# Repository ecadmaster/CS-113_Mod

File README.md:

# Modernización del Manipulador Robótico CS-113 / RS-2200 Pro-Arm

Este proyecto tiene como objetivo la recuperación y actualización tecnológica de los brazos robóticos CS-113 (RS-2200 Pro-Arm) pertenecientes a la [Universidad de Los Andes (ULA)](http://ula.ve/). Mediante el estudio del esquema original y la migración a herramientas modernas como [KiCad EDA](https://www.kicad.org/), se ha diseñado un método para interceptar el bus de control original y sustituir el microprocesador [Zilog Z80](https://www.zilog.com/docs/z80/um0080.pdf) por [microcontroladores](https://es.wikipedia.org/wiki/Microcontrolador)/[SoC](https://es.wikipedia.org/wiki/Sistema_en_un_chip) de nueva generación.

## Descripción del Proyecto

Los manipuladores robóticos CS-113 fueron equipos estándar en laboratorios de robótica, pero su dependencia del [puerto paralelo (LPT)](https://es.wikipedia.org/wiki/Puerto_paralelo) y del microprocesador Z80 los hace difícilmente integrables en entornos actuales.

Este desarrollo propone:

- Ingeniería Inversa: Estudio del esquema original de la placa rotulada como DT-001.
- Migración CAD: Reconstrucción del esquema en KiCad EDA para facilitar el análisis de interconexiones.
- Intercepción de Bus: Remoción de los [ICs](https://es.wikipedia.org/wiki/Circuito_integrado) [Zilog Z80](https://www.zilog.com/docs/z80/um0080.pdf) ($$C4$$ renombrado como $$uC4$$) y [74LS04](https://www.ti.com/lit/ds/symlink/sn74ls04.pdf) ($$D7$$ renombrado como $$uD7$$) para inyectar señales de control desde un controlador externo.
- Control Moderno: Uso de una tarjeta [MikroElectronika EasyPIC6](https://www.microchip.com/en-us/development-tool/tmik003) actualizada con un microcontrolador [Microchip PIC18F46K40](https://www.microchip.com/en-us/product/pic18f46k40).

## Esquemas

La [placa base](https://es.wikipedia.org/wiki/Circuito_impreso) del manipulador se encuentra ubicada por la parte inferior del mismo.

### Esquema original

El circuito disponible en la pagina #13 del documento [RS-2200_Pro-Arm_Robotics](datasheet/RS-2200_Pro-Arm_Robotics.pdf), entre otros valores interesantes que se logran conseguir allí de éste aparato.

### Esquema migrado a KiCad EDA

El esquema migrado a una herramienta de diseño es como sigue:

## Hardware y Modificaciones

### Componentes Reutilizados (Bloque de Potencia)

La placa original utiliza una arquitectura lógica robusta que se mantiene para el manejo de los motores, para ello se requiere la comprensión de los siguientes elementos:

- [74LS245](https://www.ti.com/lit/ds/symlink/sn74ls245.pdf): Transceptores de bus octales.
- [74LS138](https://www.ti.com/lit/ds/symlink/sn74ls138.pdf): Decodificador/demultiplexor de 3 a 8 líneas.
- [74LS75](https://www.ti.com/lit/ds/symlink/sn74ls75.pdf): Latches biestables de 4 bits.
- [TD62064AP](https://mm.digikey.com/Volume0/opasdata/d220001/medias/docus/932/TD62064AP%2CAF.pdf): Drivers [Darlington](https://es.wikipedia.org/wiki/Transistor_Darlington) de alta corriente para los [motores paso a paso (Stepper)](https://es.wikipedia.org/wiki/Motor_paso_a_paso) de tipo unipolar.

Una vez consolidado ese estudio y analizando la etapa de potencia, prácticamente solo se requiere el uso de lo siguiente:

Lo anterior sugiere que los IC: $$uC7$$, $$uE1$$, $$uE2$$, $$uE3$$, $$uE4$$, $$uE5$$, $$uE6$$, $$uE7$$, $$uF0$$, $$uF1$$, $$uF2$$, $$uF3$$, $$uF4$$, $$uF5$$, $$uF6$$, $$uF7$$ y $$uF8$$ deban estar debidamente colocados.

Tambien es requerido remover los ICs: $$uA6$$, $$uA8$$, $$uB8$$, $$uC4$$(Z80), $$uD1$$, $$uD3$$, $$uD4$$, $$uD6$$ y $$uD7$$ y $$uD7$$ para no interferir con las señales externas que provengan del controlador externo.

### Interfaz de Conexión (DB9 Personalizado)

Se ha implementado una conexión mediante un conector DB9 macho para el control de los 6 motores de paso y funciones adicionales:

| DB9 Macho | Etiqueta | Conexión |
| :----------- | :----------- | :----------- |
| Pin 1	| d0 | $$uC4$$ pin #14 |
| Pin 2	| d1 | $$uC4$$ pin #15 |
| Pin 3	| d2 | $$uC4$$ pin #12 |
| Pin 4	| d3 | $$uC4$$ pin #8 |
| Pin 5	| d4 | $$uC4$$ pin #7 |
| Pin 6	| d5 | $$uC4$$ pin #9 |
| Pin 7	| d6 | $$uC4$$ pin #10 |
| Pin 8	| ENdrv | $$uD7$$ pin #4 |
| Pin 9	| GND | $$uD7$$ pin #7 |

Quedando la modificación como sigue:

Una propuesta de adaptación en la parte trasera es como sigue:

El circuito que maneja el tren de potencia funciona con 5V TTL dado que todas las señales son de tipo entrada. Pueden conectarse controladores que funcionen a 3.3V directo sin necesidad de circuitos de interfaz, considere revisar los voltajes admitidos, ver [Logic Guide](https://www.ti.com/lit/sg/sdyu001ab/sdyu001ab.pdf) (de Texas Instruments) para mayor detalle y videoclase [Circuitos Interfaz](https://youtu.be/W1FWi5FtGR8).

## Desarrollo de Software

El firmware actual está siendo desarrollado para el [PIC18F46K40](https://www.microchip.com/en-us/product/pic18f46k40) utilizando:

- [MPLAB X IDE](https://www.microchip.com/en-us/tools-resources/develop/mplab-x-ide) con compilador [XC8](https://www.microchip.com/en-us/tools-resources/develop/mplab-xc-compilers/xc8).
- [MPLAB Code Configurator (MCC)](https://www.microchip.com/en-us/tools-resources/configure/mplab-code-configurator) para la configuración de periféricos.
- Capacidad de operación autónoma, asistida o vía [USB](https://es.wikipedia.org/wiki/Universal_Serial_Bus).

## Enlaces de Interés y Referencias

Proyectos y documentación relacionada que han servido de base:

- [Repositorio Digital ULA, Diseño e implementación de tarjeta de control para un brazo robotico CS-113, que se controle via USB](http://bdigital2.ula.ve:8080/xmlui/handle/654321/11944)
- [Análisis Técnico ITC](https://itc.ktu.lt/index.php/ITC/article/view/985/1054)
- [Hilo en Arduino Forum - Reconstrucción CS-113](https://forum.arduino.cc/t/reconstruccion-de-robot-cs-113/483691)
- [CS-113 Service-Arm](https://openvrg.moodlehub.com/file.php/30/cyr_0204/cyr_01/robotica/cs113.htm)
- [Hackaday.io - Robot Arm CS-113 Project](https://hackaday.io/project/168093-robot-arm-cs-113-18f4550-pic-usb-pc-controller)

Nota: Si has realizado algún intento de desarrollo con este manipulador, te invitamos a colaborar agregando tu referencia en esta sección.

## Colaboradores
- [Alberto Medrano](https://github.com/ecadmaster/)
- Francisco Viloria
- Gerardo Rueda
- Luis Araujo

## Instalación y Uso

Clona el repositorio:

```git clone https://github.com/ecadmaster/CS-113_Mod.git```

Consulta las datasheets para entender los límites operativos de los integrados.

## Contribuciones y Licencia
Este proyecto está bajo la licencia MIT. Las sugerencias de mejora para el entorno académico de la Escuela de Ingeniería Eléctrica son bienvenidas.

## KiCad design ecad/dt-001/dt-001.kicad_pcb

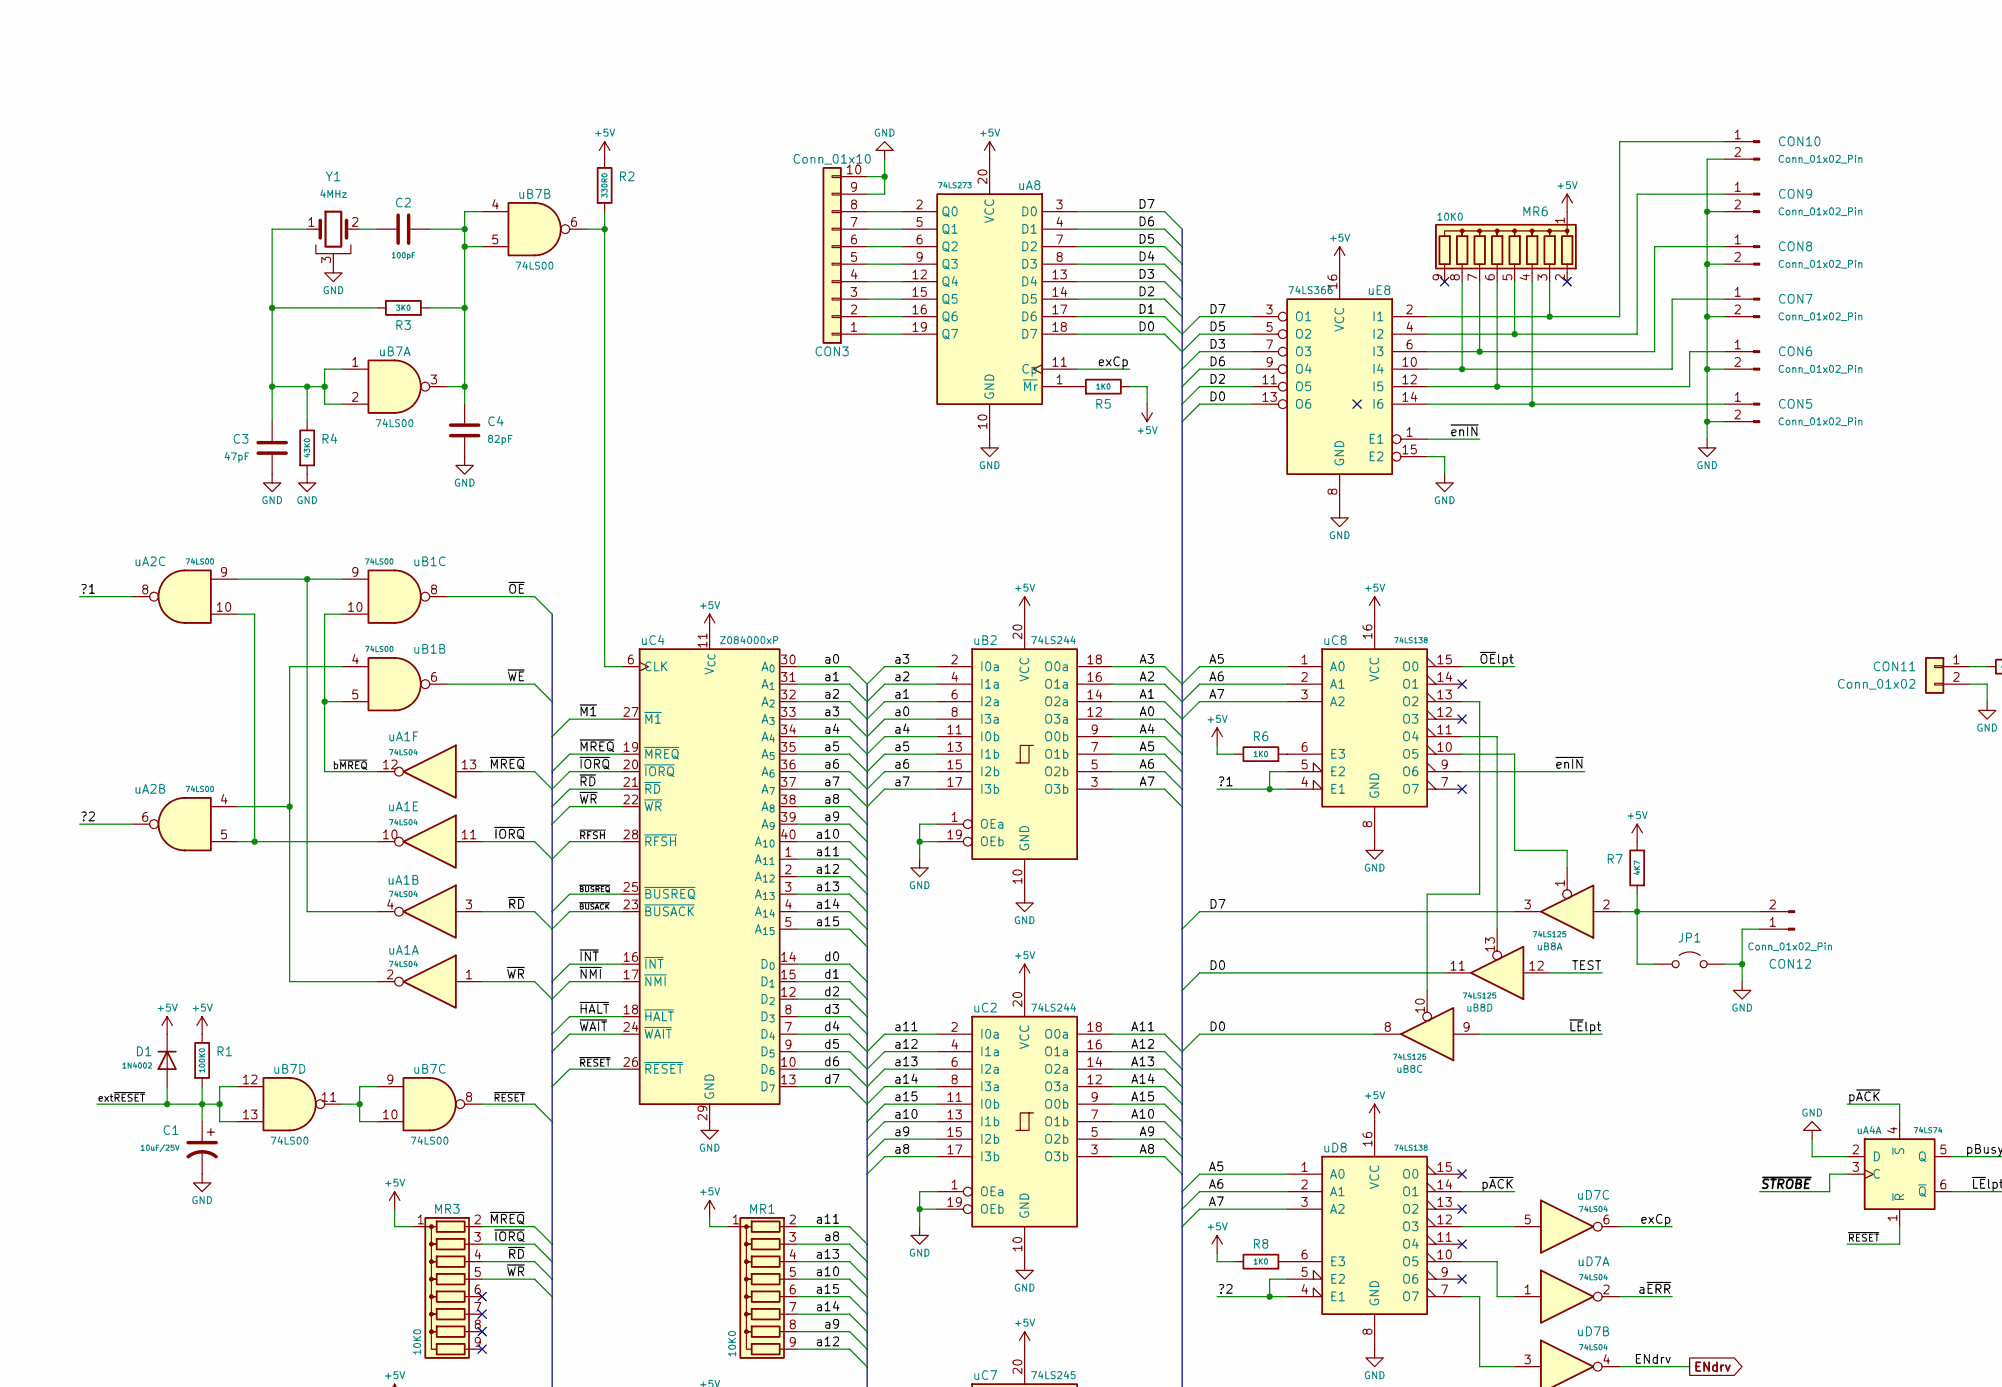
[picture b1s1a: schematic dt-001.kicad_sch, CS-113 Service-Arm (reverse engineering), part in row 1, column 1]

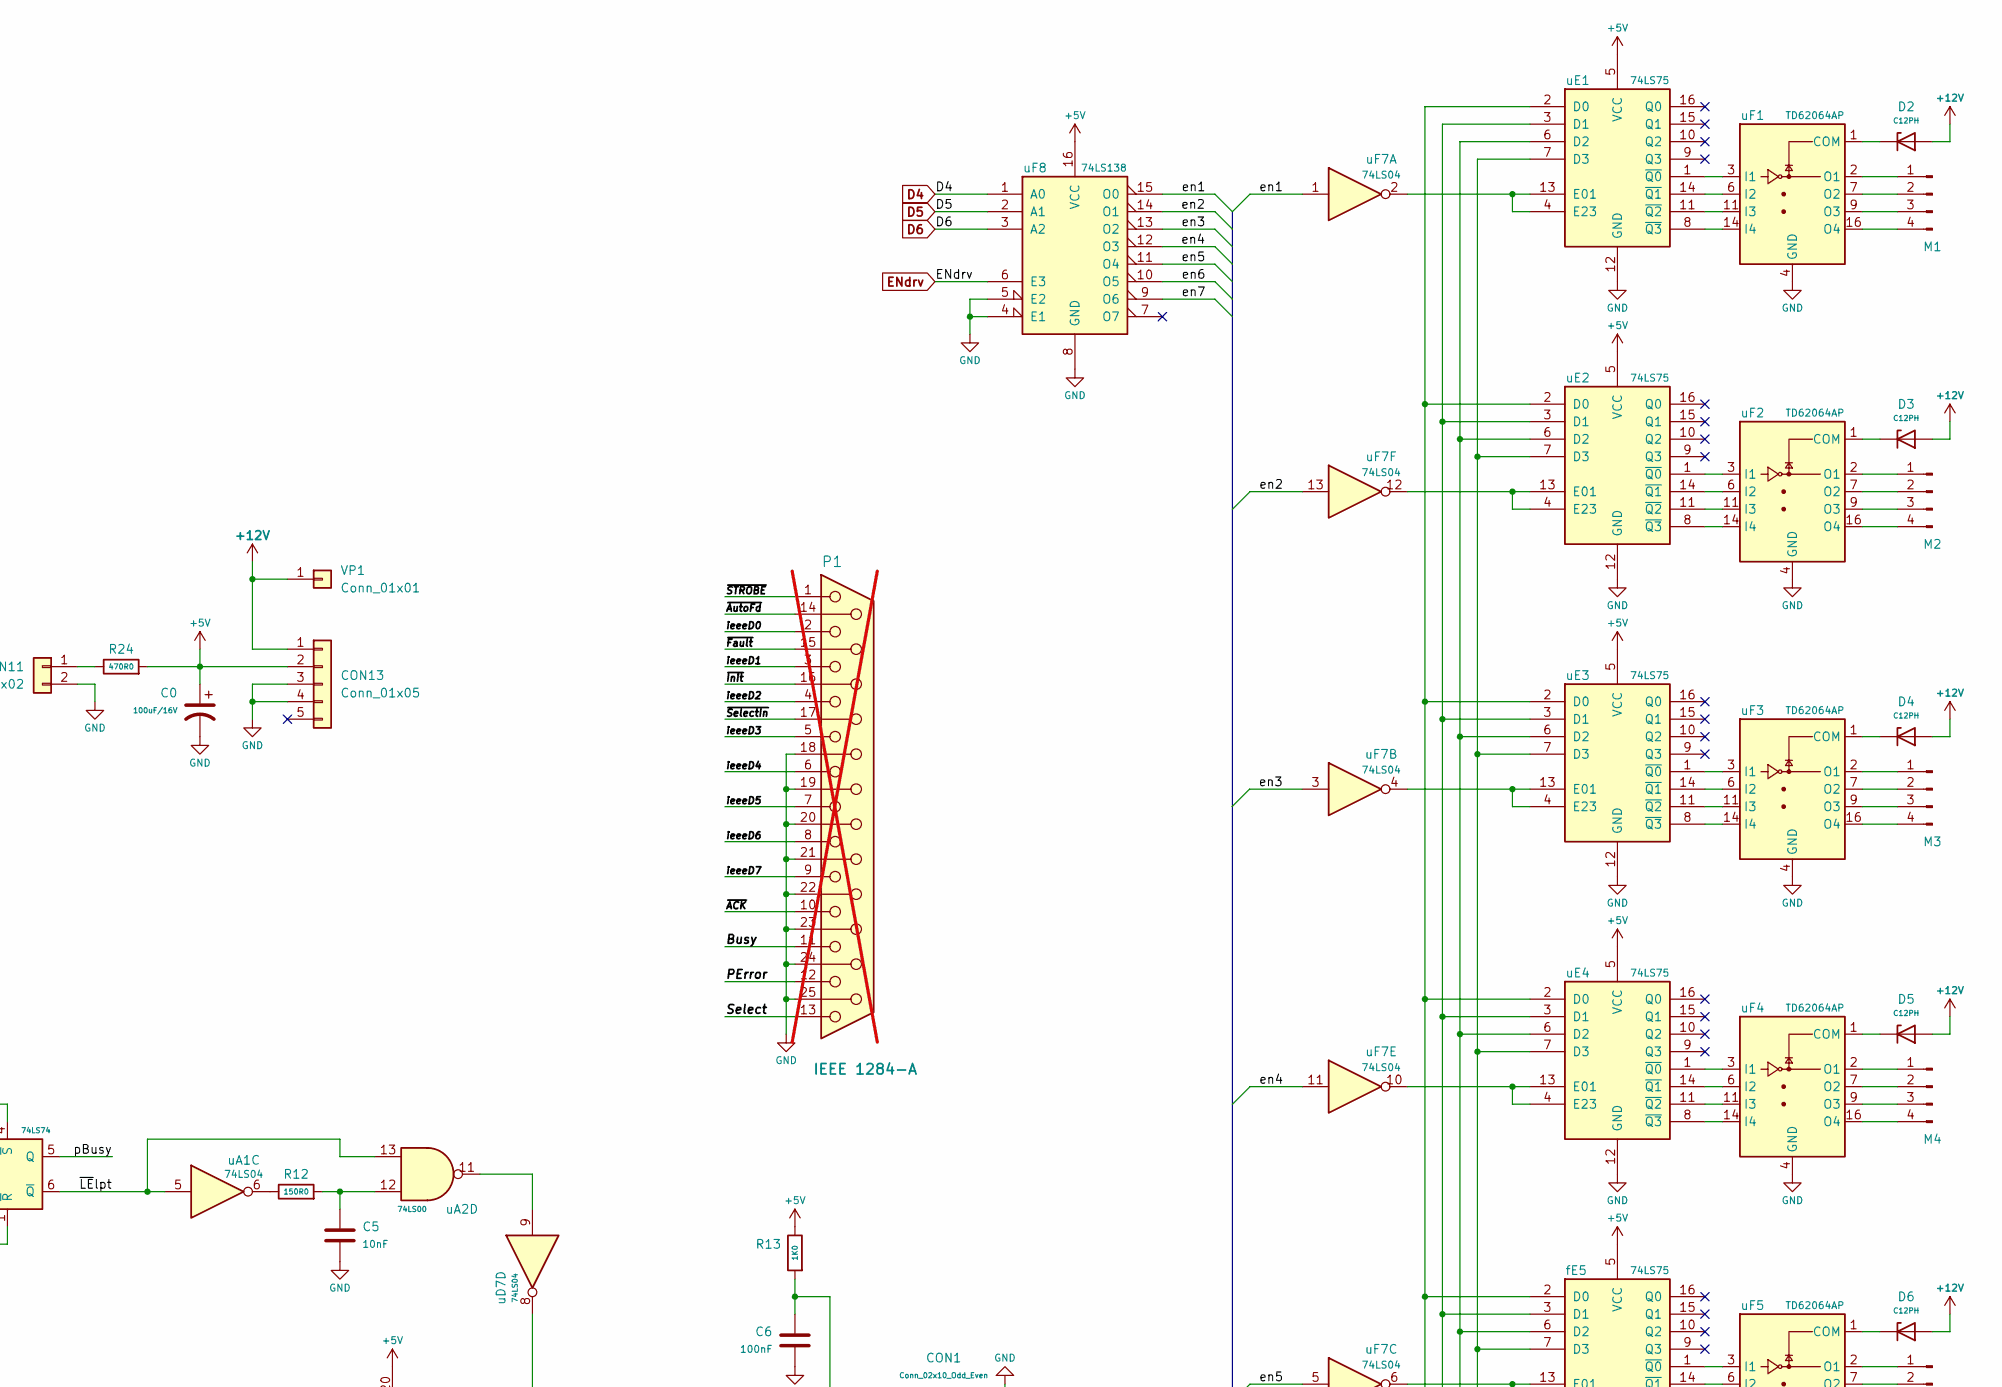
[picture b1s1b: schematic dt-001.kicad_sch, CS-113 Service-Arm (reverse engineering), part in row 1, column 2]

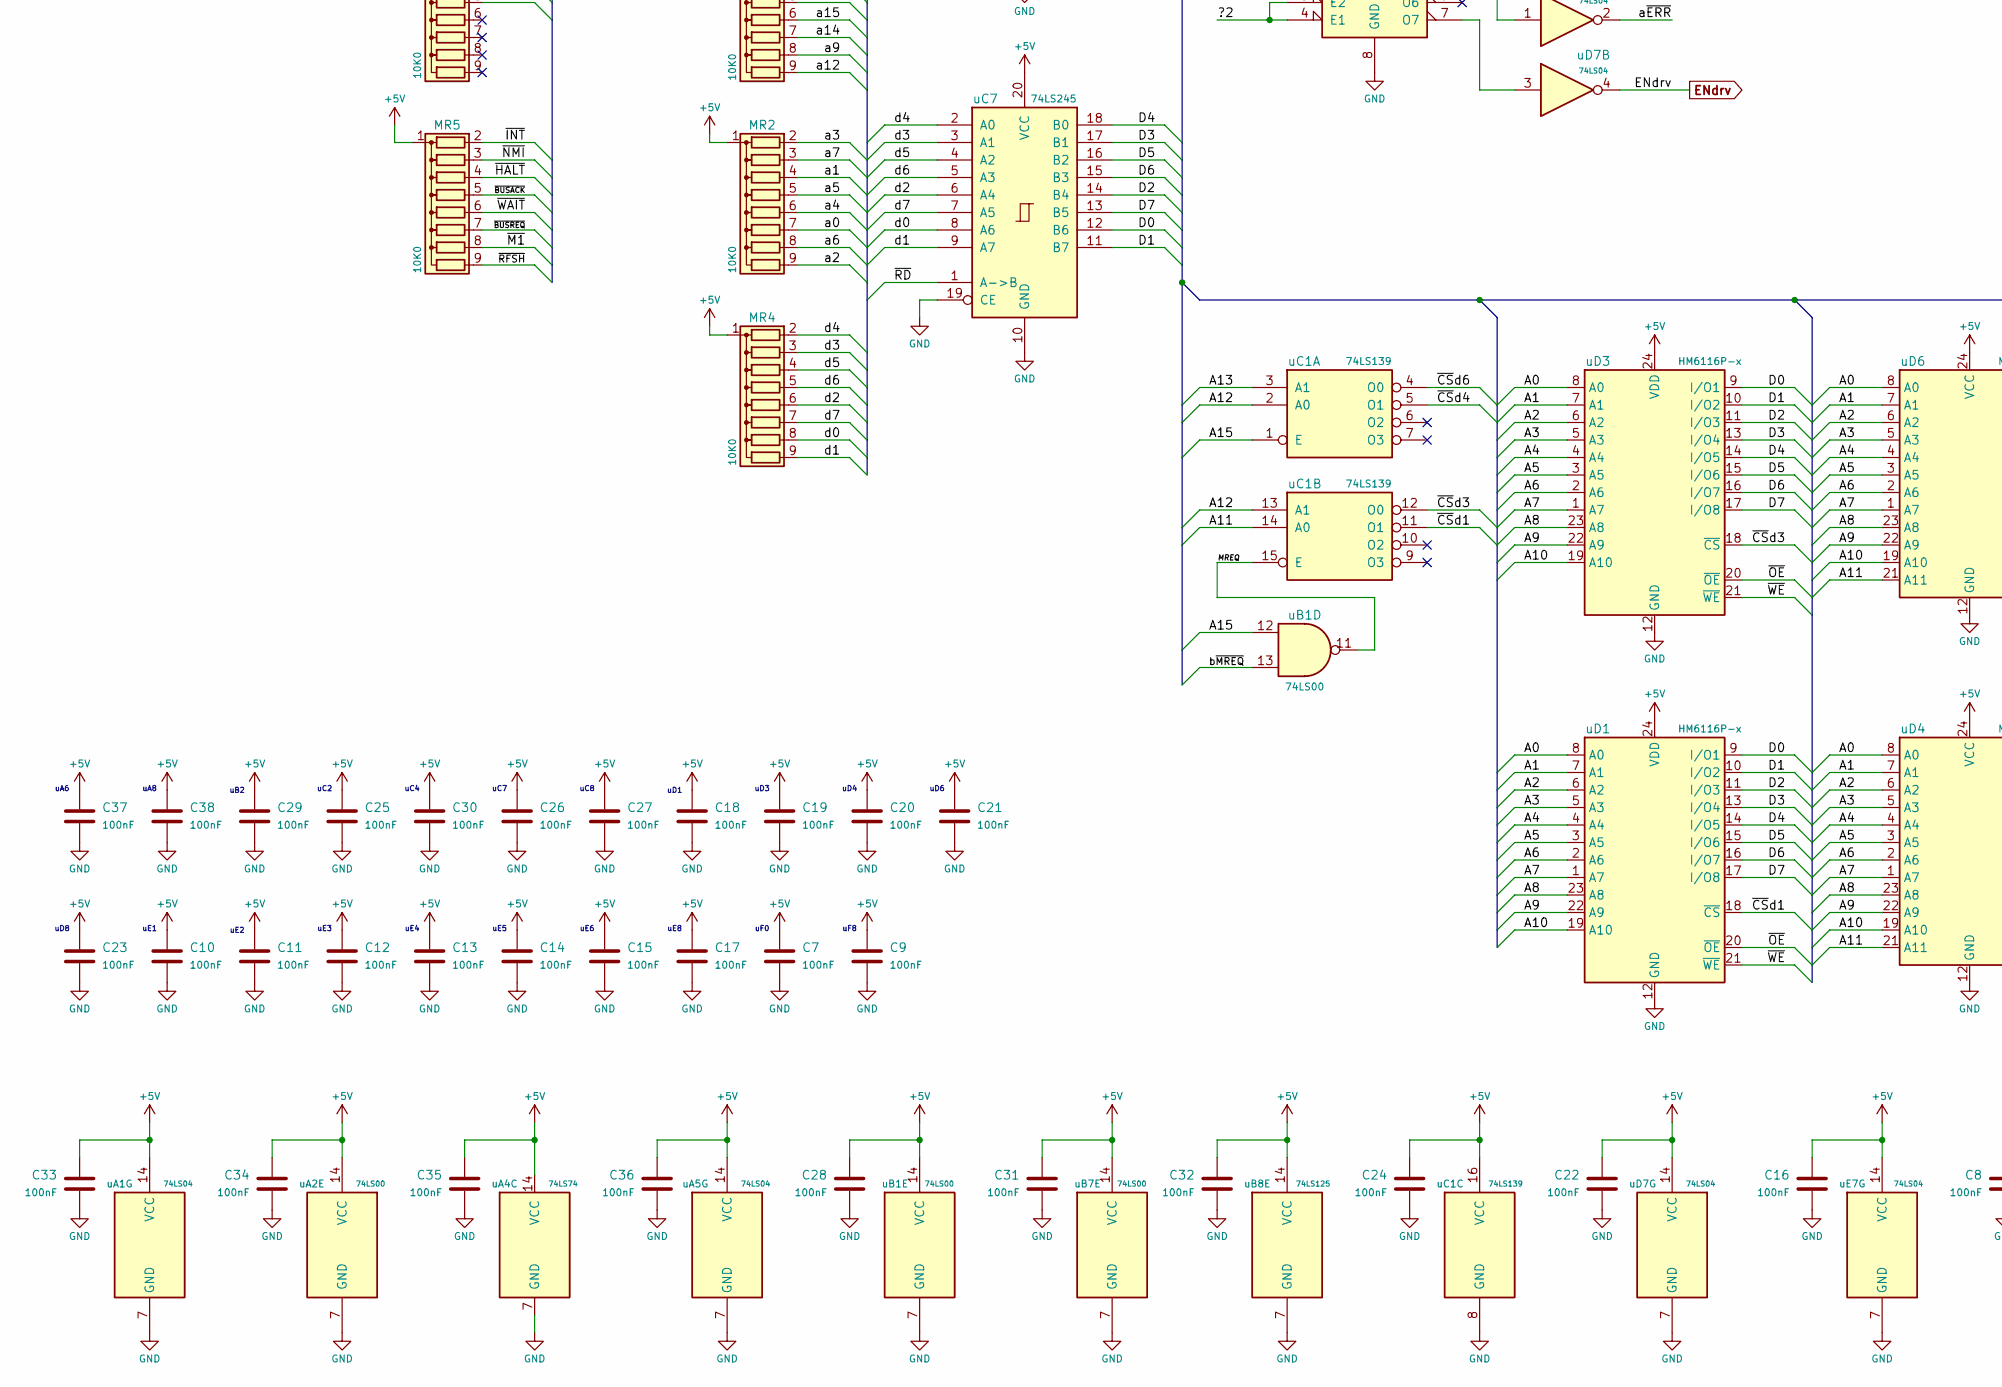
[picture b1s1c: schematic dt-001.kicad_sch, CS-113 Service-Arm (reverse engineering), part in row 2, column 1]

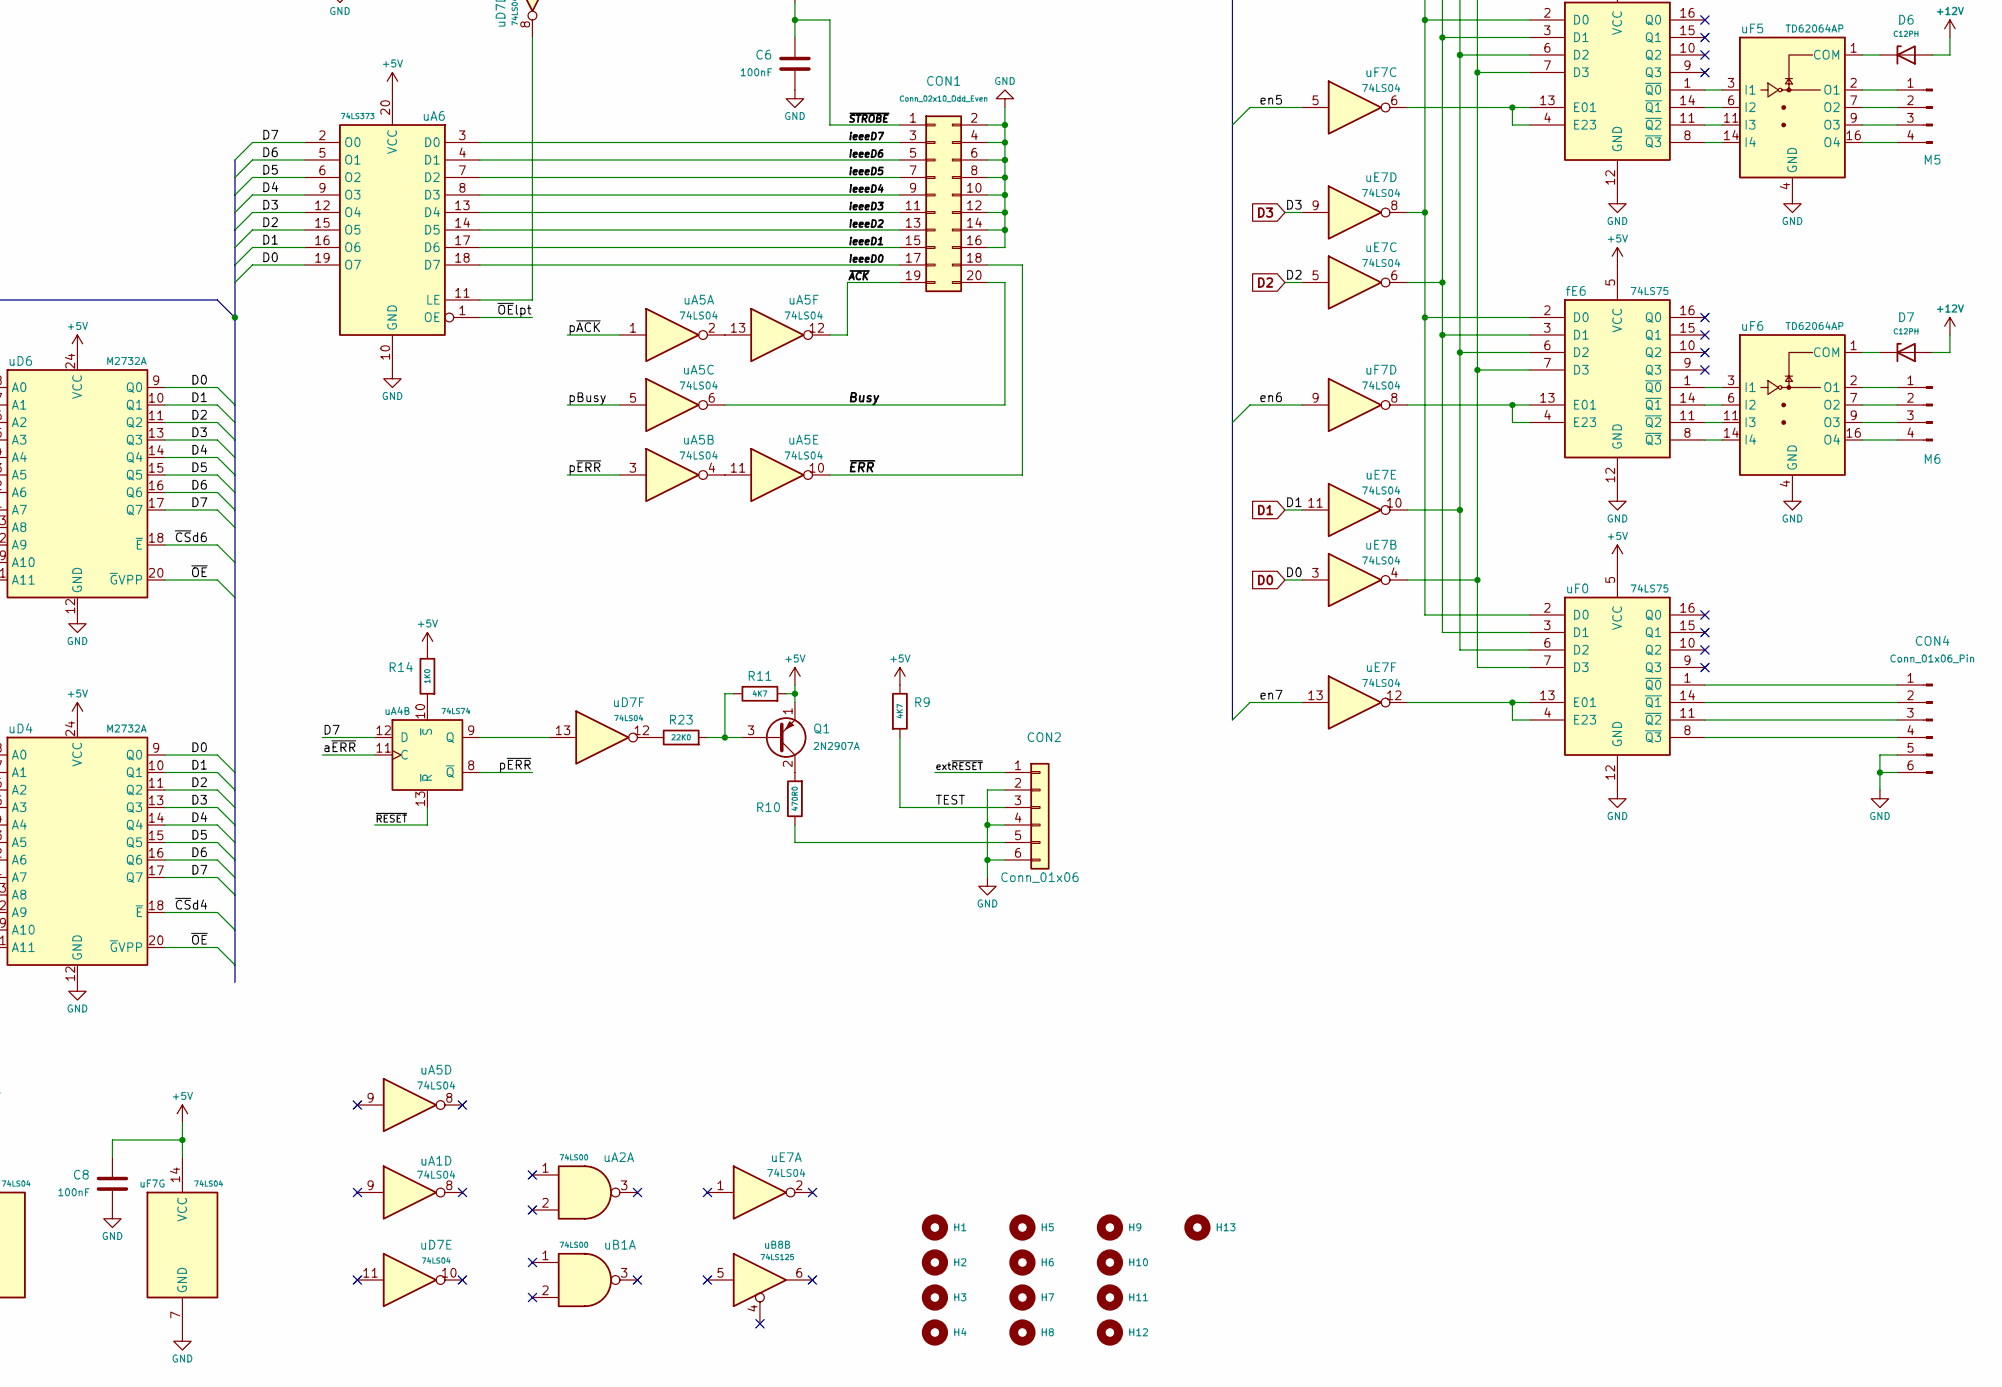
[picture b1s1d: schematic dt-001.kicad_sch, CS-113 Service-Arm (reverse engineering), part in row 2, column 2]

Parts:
C0: 100uF/16V; C_Axial_L12.0mm_D6.5mm_P20.00mm_Horizontal
C1: 10uF/25V; C_Axial_L12.0mm_D6.5mm_P20.00mm_Horizontal
C2: 100pF; C_Disc_D4.3mm_W1.9mm_P5.00mm
C3: 47pF; C_Disc_D4.3mm_W1.9mm_P5.00mm
C4: 82pF; C_Disc_D4.3mm_W1.9mm_P5.00mm
C5: 10nF; C_Disc_D4.3mm_W1.9mm_P5.00mm
C6: 100nF; C_Disc_D4.3mm_W1.9mm_P5.00mm
C7, C8, C9, C10, C11, C12, C13, C14, C15, C16, C17, C18, C19, C20, C21, C22, C23, C24, C25, C26, C27, C28, C29, C30, C31, C32, C33, C34, C35, C36, C37, C38: 100nF; C_Disc_D3.8mm_W2.6mm_P3.175mm
CON1: Conn_02x10_Odd_Even; 71922-120LF
CON2: Conn_01x06; Molex_KK-254_AE-6410-06A_1x06_P2.54mm_Vertical
CON3: Conn_01x10; Molex_KK-254_AE-6410-10A_1x10_P2.54mm_Vertical
CON4: Conn_01x06_Pin; Molex_KK-254_AE-6410-06A_1x06_P2.54mm_Vertical
CON5, CON6, CON7, CON8, CON9, CON10, CON12: Conn_01x02_Pin; Molex_KK-254_AE-6410-02A_1x02_P2.54mm_Vertical
CON11: Conn_01x02; Molex_KK-254_AE-6410-02A_1x02_P2.54mm_Vertical
CON13: Conn_01x05; Molex_KK-396_26605050_1x05_P3.96mm_Horizontal
D1: 1N4002; D_DO-41_SOD81_P10.16mm_Horizontal
D2, D3, D4, D5, D6, D7: C12PH; D_DO-41_SOD81_P10.16mm_Horizontal
H1, H2, H3, H4, H5, H6, H7, H8, H9, H10, H11, H12, H13: MountingHole; MountingHole_3.2mm_M3
JP1: Jumper_2_Open; SolderJumper-2_P1.3mm_Open_RoundedPad1.0x1.5mm
M1, M2, M3, M4, M5, M6: Conn_01x04_Pin; Molex_KK-254_AE-6410-04A_1x04_P2.54mm_Vertical
MR1, MR2, MR3, MR4, MR5, MR6: 10K0; R_Array_SIP9
P1: IEEE 1284-A; not fitted
Q1: 2N2907A; TO-18-3
R1: 100K0; R_Axial_DIN0207_L6.3mm_D2.5mm_P10.16mm_Horizontal
R2: 330R0; R_Axial_DIN0207_L6.3mm_D2.5mm_P10.16mm_Horizontal
R3: 3K0; R_Axial_DIN0207_L6.3mm_D2.5mm_P10.16mm_Horizontal
R4: 43K0; R_Axial_DIN0207_L6.3mm_D2.5mm_P10.16mm_Horizontal
R5, R6, R8, R13, R14: 1K0; R_Axial_DIN0207_L6.3mm_D2.5mm_P10.16mm_Horizontal
R7, R9, R11: 4K7; R_Axial_DIN0207_L6.3mm_D2.5mm_P10.16mm_Horizontal
R10, R24: 470R0; R_Axial_DIN0207_L6.3mm_D2.5mm_P10.16mm_Horizontal
R12: 150R0; R_Axial_DIN0207_L6.3mm_D2.5mm_P10.16mm_Horizontal
R23: 22K0; R_Axial_DIN0207_L6.3mm_D2.5mm_P10.16mm_Horizontal
VP1: Conn_01x01; PinHeader_1x01_P2.54mm_Vertical
Y1: 4MHz; Crystal_HC49-U_Horizontal_1EP_style1
fE5, fE6: 74LS75; DIP-16_W7.62mm
uA1, uA5: 74LS04; DIP-14_W7.62mm
uA2: 74LS00; DIP-14_W7.62mm
uA4: 74LS74; DIP-14_W7.62mm
uA6: 74LS373; DIP-20_W7.62mm
uA8: 74LS273; DIP-20_W7.62mm
uB1, uB7: 74LS00; DIP-14_W7.62mm
uB2: 74LS244; DIP-20_W7.62mm
uB8: 74LS125; DIP-14_W7.62mm
uC1: 74LS139; DIP-16_W7.62mm
uC2: 74LS244; DIP-20_W7.62mm
uC4: Z084000xP; DIP-40_W15.24mm
uC7: 74LS245; DIP-20_W7.62mm
uC8: 74LS138; DIP-16_W7.62mm
uD1, uD3: HM6116P-x; DIP-24_W15.24mm
uD4, uD6: M2732A; DIP-24_W15.24mm
uD7: 74LS04; DIP-14_W7.62mm
uD8: 74LS138; DIP-16_W7.62mm
uE1, uE2, uE3, uE4: 74LS75; DIP-16_W7.62mm
uE7: 74LS04; DIP-14_W7.62mm
uE8: 74LS366; DIP-16_W7.62mm
uF0: 74LS75; DIP-16_W7.62mm
uF1, uF2, uF3, uF4, uF5, uF6: TD62064AP; DIP-16_W7.62mm
uF7: 74LS04; DIP-14_W7.62mm
uF8: 74LS138; DIP-16_W7.62mm

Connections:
+5V: C0.1, C7.1, C8.1, C9.1, C10.1, C11.1, C12.1, C13.1, C14.1, C15.1, C16.1, C17.1, C18.1, C19.1, C20.1, C21.1, C22.1, C23.1, C24.1, C25.1, C26.1, C27.1, C28.1, C29.1, C30.1, C31.1, C32.1, C33.1, C34.1, C35.1, C36.1, C37.1, C38.1, CON13.2, D1.1 (K), MR1.1 (common), MR2.1 (common), MR3.1 (common), MR4.1 (common), MR5.1 (common), MR6.1 (common), Q1.1 (E), R1.1, R2.1, R5.1, R6.1, R7.1, R8.1, R9.1, R11.2, R13.1, R14.1, R24.2, fE5.5 (VCC), fE6.5 (VCC), uA1.14 (VCC), uA2.14 (VCC), uA4.14 (VCC), uA5.14 (VCC), uA6.20 (VCC), uA8.20 (VCC), uB1.14 (VCC), uB2.20 (VCC), uB7.14 (VCC), uB8.14 (VCC), uC1.16 (VCC), uC2.20 (VCC), uC4.11 (V_{CC}), uC7.20 (VCC), uC8.16 (VCC), uD1.24 (VDD), uD3.24 (VDD), uD4.24 (VCC), uD6.24 (VCC), uD7.14 (VCC), uD8.16 (VCC), uE1.5 (VCC), uE2.5 (VCC), uE3.5 (VCC), uE4.5 (VCC), uE7.14 (VCC), uE8.16 (VCC), uF0.5 (VCC), uF7.14 (VCC), uF8.16 (VCC)
+12V: CON13.1, D2.2 (A), D3.2 (A), D4.2 (A), D5.2 (A), D6.2 (A), D7.2 (A), VP1.1 (Pin_1_1)
/?1: uA2.8, uC8.4 (E1), uC8.5 (E2)
/?2: uA2.6, uD8.4 (E1), uD8.5 (E2)
/A0: uB2.12 (O3a), uD1.8 (A0), uD3.8 (A0), uD4.8 (A0), uD6.8 (A0)
/A1: uB2.14 (O2a), uD1.7 (A1), uD3.7 (A1), uD4.7 (A1), uD6.7 (A1)
/A2: uB2.16 (O1a), uD1.6 (A2), uD3.6 (A2), uD4.6 (A2), uD6.6 (A2)
/A3: uB2.18 (O0a), uD1.5 (A3), uD3.5 (A3), uD4.5 (A3), uD6.5 (A3)
/A4: uB2.9 (O0b), uD1.4 (A4), uD3.4 (A4), uD4.4 (A4), uD6.4 (A4)
/A5: uB2.7 (O1b), uC8.1 (A0), uD1.3 (A5), uD3.3 (A5), uD4.3 (A5), uD6.3 (A5), uD8.1 (A0)
/A6: uB2.5 (O2b), uC8.2 (A1), uD1.2 (A6), uD3.2 (A6), uD4.2 (A6), uD6.2 (A6), uD8.2 (A1)
/A7: uB2.3 (O3b), uC8.3 (A2), uD1.1 (A7), uD3.1 (A7), uD4.1 (A7), uD6.1 (A7), uD8.3 (A2)
/A8: uC2.3 (O3b), uD1.23 (A8), uD3.23 (A8), uD4.23 (A8), uD6.23 (A8)
/A9: uC2.5 (O2b), uD1.22 (A9), uD3.22 (A9), uD4.22 (A9), uD6.22 (A9)
/A10: uC2.7 (O1b), uD1.19 (A10), uD3.19 (A10), uD4.19 (A10), uD6.19 (A10)
/A11: uC1.14 (A0), uC2.18 (O0a), uD4.21 (A11), uD6.21 (A11)
/A12: uC1.2 (A0), uC1.13 (A1), uC2.16 (O1a)
/A13: uC1.3 (A1), uC2.14 (O2a)
/A14: uC2.12 (O3a)
/A15: uB1.12, uC1.1 (E), uC2.9 (O0b)
/Busy: CON1.20, P1.11, uA5.6
/D7: uA4.12 (D), uA6.2 (O0), uA8.3 (D0), uB8.3, uC7.13 (B5), uD1.17 (I/O8), uD3.17 (I/O8), uD4.17 (Q7), uD6.17 (Q7), uE8.3 (O1)
/MREQ: uB1.11, uC1.15 (E)
/TEST: CON2.3, R9.2, uB8.12
/a0: MR2.7 (R6), uB2.8 (I3a), uC4.30 (A_{0})
/a1: MR2.4 (R3), uB2.6 (I2a), uC4.31 (A_{1})
/a2: MR2.9 (R8), uB2.4 (I1a), uC4.32 (A_{2})
/a3: MR2.2 (R1), uB2.2 (I0a), uC4.33 (A_{3})
/a4: MR2.6 (R5), uB2.11 (I0b), uC4.34 (A_{4})
/a5: MR2.5 (R4), uB2.13 (I1b), uC4.35 (A_{5})
/a6: MR2.8 (R7), uB2.15 (I2b), uC4.36 (A_{6})
/a7: MR2.3 (R2), uB2.17 (I3b), uC4.37 (A_{7})
/a8: MR1.3 (R2), uC2.17 (I3b), uC4.38 (A_{8})
/a9: MR1.8 (R7), uC2.15 (I2b), uC4.39 (A_{9})
/a10: MR1.5 (R4), uC2.13 (I1b), uC4.40 (A_{10})
/a11: MR1.2 (R1), uC2.2 (I0a), uC4.1 (A_{11})
/a12: MR1.9 (R8), uC2.4 (I1a), uC4.2 (A_{12})
/a13: MR1.4 (R3), uC2.6 (I2a), uC4.3 (A_{13})
/a14: MR1.7 (R6), uC2.8 (I3a), uC4.4 (A_{14})
/a15: MR1.6 (R5), uC2.11 (I0b), uC4.5 (A_{15})
/a~ERR: uA4.11 (C), uD7.2
/b~MREQ: uA1.12, uB1.5, uB1.10, uB1.13
/d0: MR4.8 (R7), uC4.14 (D_{0}), uC7.8 (A6)
/d1: MR4.9 (R8), uC4.15 (D_{1}), uC7.9 (A7)
/d2: MR4.6 (R5), uC4.12 (D_{2}), uC7.6 (A4)
/d3: MR4.3 (R2), uC4.8 (D_{3}), uC7.3 (A1)
/d4: MR4.2 (R1), uC4.7 (D_{4}), uC7.2 (A0)
/d5: MR4.4 (R3), uC4.9 (D_{5}), uC7.4 (A2)
/d6: MR4.5 (R4), uC4.10 (D_{6}), uC7.5 (A3)
/d7: MR4.7 (R6), uC4.13 (D_{7}), uC7.7 (A5)
/en1: uF7.1, uF8.15 (O0)
/en2: uF7.13, uF8.14 (O1)
/en3: uF8.13 (O2)
/en4: uF7.11, uF8.12 (O3)
/en5: uF7.5, uF8.11 (O4)
/en6: uF7.9, uF8.10 (O5)
/en7: uE7.13, uF8.9 (O6)
/exCp: uA8.11 (Cp), uD7.6
/ext~RESET: C1.1, CON2.1, D1.2 (A), R1.2, uB7.12, uB7.13
/ieeeD0: CON1.17, P1.2, uA6.18 (D7)
/ieeeD1: CON1.15, P1.3, uA6.17 (D6)
/ieeeD2: CON1.13, P1.4, uA6.14 (D5)
/ieeeD3: CON1.11, P1.5, uA6.13 (D4)
/ieeeD4: CON1.9, P1.6, uA6.8 (D3)
/ieeeD5: CON1.7, P1.7, uA6.7 (D2)
/ieeeD6: CON1.5, P1.8, uA6.4 (D1)
/ieeeD7: CON1.3, P1.9, uA6.3 (D0)
/pBusy: uA4.5 (Q), uA5.5
/p~ACK: uA4.4 (~S), uA5.1, uD8.14 (O1)
/p~ERR: uA4.8 (~Q), uA5.3
/~ACK: CON1.19, P1.10, uA5.12
/~BUSACK: MR5.5 (R4), uC4.23 (~BUSACK)
/~BUSREQ: MR5.7 (R6), uC4.25 (~BUSREQ)
/~CSd1: uC1.11 (O1), uD1.18 (~CS)
/~CSd3: uC1.12 (O0), uD3.18 (~CS)
/~CSd4: uC1.5 (O1), uD4.18 (~E)
/~CSd6: uC1.4 (O0), uD6.18 (~E)
/~ERR: CON1.18, uA5.10
/~HALT: MR5.4 (R3), uC4.18 (~HALT)
/~INT: MR5.2 (R1), uC4.16 (~INT)
/~IORQ: MR3.3 (R2), uA1.11, uC4.20 (~IORQ)
/~LElpt: uA1.5, uA2.13, uA4.6 (~Q), uB8.9
/~M1: MR5.8 (R7), uC4.27 (~M1)
/~MREQ: MR3.2 (R1), uA1.13, uC4.19 (~MREQ)
/~NMI: MR5.3 (R2), uC4.17 (~NMI)
/~OE: uB1.8, uD1.20 (~OE), uD3.20 (~OE), uD4.20 (~GVPP), uD6.20 (~GVPP)
/~OElpt: uA6.1 (OE), uC8.15 (O0)
/~RD: MR3.4 (R3), uA1.3, uC4.21 (~RD), uC7.1 (A->B)
/~RESET: uA4.1 (~R), uA4.13 (~R), uB7.8, uC4.26 (~RESET)
/~RFSH: MR5.9 (R8), uC4.28 (~RFSH)
/~STROBE: C6.1, CON1.1, P1.1, R13.2, uA4.3 (C)
/~WAIT: MR5.6 (R5), uC4.24 (~WAIT)
/~WE: uB1.6, uD1.21 (~WE), uD3.21 (~WE)
/~WR: MR3.5 (R4), uA1.1, uC4.22 (~WR)
/~enIN: uC8.9 (O6), uE8.1 (E1)
D0: uA6.19 (O7), uA8.18 (D7), uB8.8, uB8.11, uC7.12 (B6), uD1.9 (I/O1), uD3.9 (I/O1), uD4.9 (Q0), uD6.9 (Q0), uE7.3, uE8.13 (O6)
D1: uA6.16 (O6), uA8.17 (D6), uC7.11 (B7), uD1.10 (I/O2), uD3.10 (I/O2), uD4.10 (Q1), uD6.10 (Q1), uE7.11
D2: uA6.15 (O5), uA8.14 (D5), uC7.14 (B4), uD1.11 (I/O3), uD3.11 (I/O3), uD4.11 (Q2), uD6.11 (Q2), uE7.5, uE8.11 (O5)
D3: uA6.12 (O4), uA8.13 (D4), uC7.17 (B1), uD1.13 (I/O4), uD3.13 (I/O4), uD4.13 (Q3), uD6.13 (Q3), uE7.9, uE8.7 (O3)
D4: uA6.9 (O3), uA8.8 (D3), uC7.18 (B0), uD1.14 (I/O5), uD3.14 (I/O5), uD4.14 (Q4), uD6.14 (Q4), uF8.1 (A0)
D5: uA6.6 (O2), uA8.7 (D2), uC7.16 (B2), uD1.15 (I/O6), uD3.15 (I/O6), uD4.15 (Q5), uD6.15 (Q5), uE8.5 (O2), uF8.2 (A1)
D6: uA6.5 (O1), uA8.4 (D1), uC7.15 (B3), uD1.16 (I/O7), uD3.16 (I/O7), uD4.16 (Q6), uD6.16 (Q6), uE8.9 (O4), uF8.3 (A2)
ENdrv: uD7.4, uF8.6 (E3)
GND: C0.2, C1.2, C3.2, C4.2, C5.2, C6.2, C7.2, C8.2, C9.2, C10.2, C11.2, C12.2, C13.2, C14.2, C15.2, C16.2, C17.2, C18.2, C19.2, C20.2, C21.2, C22.2, C23.2, C24.2, C25.2, C26.2, C27.2, C28.2, C29.2, C30.2, C31.2, C32.2, C33.2, C34.2, C35.2, C36.2, C37.2, C38.2, CON1.2, CON1.4, CON1.6, CON1.8, CON1.10, CON1.12, CON1.14, CON1.16, CON2.2, CON2.4, CON2.6, CON3.9, CON3.10, CON4.5, CON4.6, CON5.2, CON6.2, CON7.2, CON8.2, CON9.2, CON10.2, CON11.2, CON12.1, CON13.3, CON13.4, JP1.1 (A), P1.18, P1.19, P1.20, P1.21, P1.22, P1.23, P1.24, P1.25, R4.2, Y1.3, fE5.12 (GND), fE6.12 (GND), uA1.7 (GND), uA2.7 (GND), uA4.2 (D), uA4.7 (GND), uA5.7 (GND), uA6.10 (GND), uA8.10 (GND), uB1.7 (GND), uB2.1 (OEa), uB2.10 (GND), uB2.19 (OEb), uB7.7 (GND), uB8.7 (GND), uC1.8 (GND), uC2.1 (OEa), uC2.10 (GND), uC2.19 (OEb), uC4.29 (GND), uC7.10 (GND), uC7.19 (CE), uC8.8 (GND), uD1.12 (GND), uD3.12 (GND), uD4.12 (GND), uD6.12 (GND), uD7.7 (GND), uD8.8 (GND), uE1.12 (GND), uE2.12 (GND), uE3.12 (GND), uE4.12 (GND), uE7.7 (GND), uE8.8 (GND), uE8.15 (E2), uF0.12 (GND), uF1.4 (GND), uF1.5 (GND), uF1.12 (GND), uF1.13 (GND), uF2.4 (GND), uF2.5 (GND), uF2.12 (GND), uF2.13 (GND), uF3.4 (GND), uF3.5 (GND), uF3.12 (GND), uF3.13 (GND), uF4.4 (GND), uF4.5 (GND), uF4.12 (GND), uF4.13 (GND), uF5.4 (GND), uF5.5 (GND), uF5.12 (GND), uF5.13 (GND), uF6.4 (GND), uF6.5 (GND), uF6.12 (GND), uF6.13 (GND), uF7.7 (GND), uF8.4 (E1), uF8.5 (E2), uF8.8 (GND)
unnamed: C2.1, Y1.2
unnamed: C2.2, C4.1, R3.2, uB7.3, uB7.4, uB7.5
unnamed: C3.1, R3.1, R4.1, Y1.1, uB7.1, uB7.2
unnamed: C5.1, R12.2, uA2.12
unnamed: CON2.5, R10.1
unnamed: CON3.1, uA8.19 (Q7)
unnamed: CON3.2, uA8.16 (Q6)
unnamed: CON3.3, uA8.15 (Q5)
unnamed: CON3.4, uA8.12 (Q4)
unnamed: CON3.5, uA8.9 (Q3)
unnamed: CON3.6, uA8.6 (Q2)
unnamed: CON3.7, uA8.5 (Q1)
unnamed: CON3.8, uA8.2 (Q0)
unnamed: CON4.1, uF0.1 (~Q0)
unnamed: CON4.2, uF0.14 (~Q1)
unnamed: CON4.3, uF0.11 (~Q2)
unnamed: CON4.4, uF0.8 (~Q3)
unnamed: CON5.1, MR6.4 (R3), uE8.14 (I6)
unnamed: CON6.1, MR6.6 (R5), uE8.12 (I5)
unnamed: CON7.1, MR6.8 (R7), uE8.10 (I4)
unnamed: CON8.1, MR6.7 (R6), uE8.6 (I3)
unnamed: CON9.1, MR6.5 (R4), uE8.4 (I2)
unnamed: CON10.1, MR6.3 (R2), uE8.2 (I1)
unnamed: CON11.1, R24.1
unnamed: CON12.2, JP1.2 (B), R7.2, uB8.2
unnamed: D2.1 (K), uF1.1 (COM), uF1.8 (COM)
unnamed: D3.1 (K), uF2.1 (COM), uF2.8 (COM)
unnamed: D4.1 (K), uF3.1 (COM), uF3.8 (COM)
unnamed: D5.1 (K), uF4.1 (COM), uF4.8 (COM)
unnamed: D6.1 (K), uF5.1 (COM), uF5.8 (COM)
unnamed: D7.1 (K), uF6.1 (COM), uF6.8 (COM)
unnamed: M1.1, uF1.2 (O1)
unnamed: M1.2, uF1.7 (O2)
unnamed: M1.3, uF1.9 (O3)
unnamed: M1.4, uF1.16 (O4)
unnamed: M2.1, uF2.2 (O1)
unnamed: M2.2, uF2.7 (O2)
unnamed: M2.3, uF2.9 (O3)
unnamed: M2.4, uF2.16 (O4)
unnamed: M3.1, uF3.2 (O1)
unnamed: M3.2, uF3.7 (O2)
unnamed: M3.3, uF3.9 (O3)
unnamed: M3.4, uF3.16 (O4)
unnamed: M4.1, uF4.2 (O1)
unnamed: M4.2, uF4.7 (O2)
unnamed: M4.3, uF4.9 (O3)
unnamed: M4.4, uF4.16 (O4)
unnamed: M5.1, uF5.2 (O1)
unnamed: M5.2, uF5.7 (O2)
unnamed: M5.3, uF5.9 (O3)
unnamed: M5.4, uF5.16 (O4)
unnamed: M6.1, uF6.2 (O1)
unnamed: M6.2, uF6.7 (O2)
unnamed: M6.3, uF6.9 (O3)
unnamed: M6.4, uF6.16 (O4)
unnamed: Q1.3 (B), R11.1, R23.2
unnamed: Q1.2 (C), R10.2
unnamed: R12.1, uA1.6
unnamed: R23.1, uD7.12
unnamed: fE5.2 (D0), fE6.2 (D0), uE1.2 (D0), uE2.2 (D0), uE3.2 (D0), uE4.2 (D0), uE7.8, uF0.2 (D0)
unnamed: fE5.3 (D1), fE6.3 (D1), uE1.3 (D1), uE2.3 (D1), uE3.3 (D1), uE4.3 (D1), uE7.6, uF0.3 (D1)
unnamed: fE5.6 (D2), fE6.6 (D2), uE1.6 (D2), uE2.6 (D2), uE3.6 (D2), uE4.6 (D2), uE7.10, uF0.6 (D2)
unnamed: fE5.7 (D3), fE6.7 (D3), uE1.7 (D3), uE2.7 (D3), uE3.7 (D3), uE4.7 (D3), uE7.4, uF0.7 (D3)
unnamed: fE5.4 (E23), fE5.13 (E01), uF7.6
unnamed: fE5.1 (~Q0), uF5.3 (I1)
unnamed: fE5.14 (~Q1), uF5.6 (I2)
unnamed: fE5.11 (~Q2), uF5.11 (I3)
unnamed: fE5.8 (~Q3), uF5.14 (I4)
unnamed: fE6.4 (E23), fE6.13 (E01), uF7.8
unnamed: fE6.1 (~Q0), uF6.3 (I1)
unnamed: fE6.14 (~Q1), uF6.6 (I2)
unnamed: fE6.11 (~Q2), uF6.11 (I3)
unnamed: fE6.8 (~Q3), uF6.14 (I4)
unnamed: uA1.2, uA2.4, uB1.4
unnamed: uA1.4, uA2.9, uB1.9
unnamed: uA1.10, uA2.5, uA2.10
unnamed: uA2.11, uD7.9
unnamed: uA4.9 (Q), uD7.13
unnamed: R14.2, uA4.10 (~S)
unnamed: uA5.4, uA5.11
unnamed: uA5.2, uA5.13
unnamed: uA6.11 (LE), uD7.8
unnamed: R5.2, uA8.1 (~Mr)
unnamed: uB7.9, uB7.10, uB7.11
unnamed: R2.2, uB7.6, uC4.6 (CLK)
unnamed: R6.2, uC8.6 (E3)
unnamed: uB8.10, uC8.13 (O2)
unnamed: uB8.13, uC8.11 (O4)
unnamed: uB8.1, uC8.10 (O5)
unnamed: R8.2, uD8.6 (E3)
unnamed: uD7.5, uD8.12 (O3)
unnamed: uD7.1, uD8.10 (O5)
unnamed: uD7.3, uD8.7 (O7)
unnamed: uE1.4 (E23), uE1.13 (E01), uF7.2
unnamed: uE1.1 (~Q0), uF1.3 (I1)
unnamed: uE1.14 (~Q1), uF1.6 (I2)
unnamed: uE1.11 (~Q2), uF1.11 (I3)
unnamed: uE1.8 (~Q3), uF1.14 (I4)
unnamed: uE2.4 (E23), uE2.13 (E01), uF7.12
unnamed: uE2.1 (~Q0), uF2.3 (I1)
unnamed: uE2.14 (~Q1), uF2.6 (I2)
unnamed: uE2.11 (~Q2), uF2.11 (I3)
unnamed: uE2.8 (~Q3), uF2.14 (I4)
unnamed: uE3.4 (E23), uE3.13 (E01), uF7.4
unnamed: uE3.1 (~Q0), uF3.3 (I1)
unnamed: uE3.14 (~Q1), uF3.6 (I2)
unnamed: uE3.11 (~Q2), uF3.11 (I3)
unnamed: uE3.8 (~Q3), uF3.14 (I4)
unnamed: uE4.4 (E23), uE4.13 (E01), uF7.10
unnamed: uE4.1 (~Q0), uF4.3 (I1)
unnamed: uE4.14 (~Q1), uF4.6 (I2)
unnamed: uE4.11 (~Q2), uF4.11 (I3)
unnamed: uE4.8 (~Q3), uF4.14 (I4)
unnamed: uE7.12, uF0.4 (E23), uF0.13 (E01)

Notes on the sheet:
uD8
uC8
uE6
uD3
uD1
uD6
uF8
uF0
uA6
uC7
uE5
uE8
uD4
uC2
uE1
uB2
uE2
uC4
uE3
uE4
uA8

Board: 2 copper layers, 142 parts (0 on the bottom side), 216 nets, no tracks yet.

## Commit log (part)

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2026-04-21 Primera version del esquema
2026-04-21 Agregando fotos de referencia
2026-04-21 mejorando imagen
2026-04-21 removiendo innecesarios
2026-04-21 agregando datasheet y errata
2026-04-21 agregando caracteristica de circuito sch, control de motores
2026-04-21 agregando imagen con mod cable DB9
2026-04-27 actualizacion a KiCad 10
2026-05-07 agregango panel y archivos para construccion

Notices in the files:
README.md:
License: MIT
